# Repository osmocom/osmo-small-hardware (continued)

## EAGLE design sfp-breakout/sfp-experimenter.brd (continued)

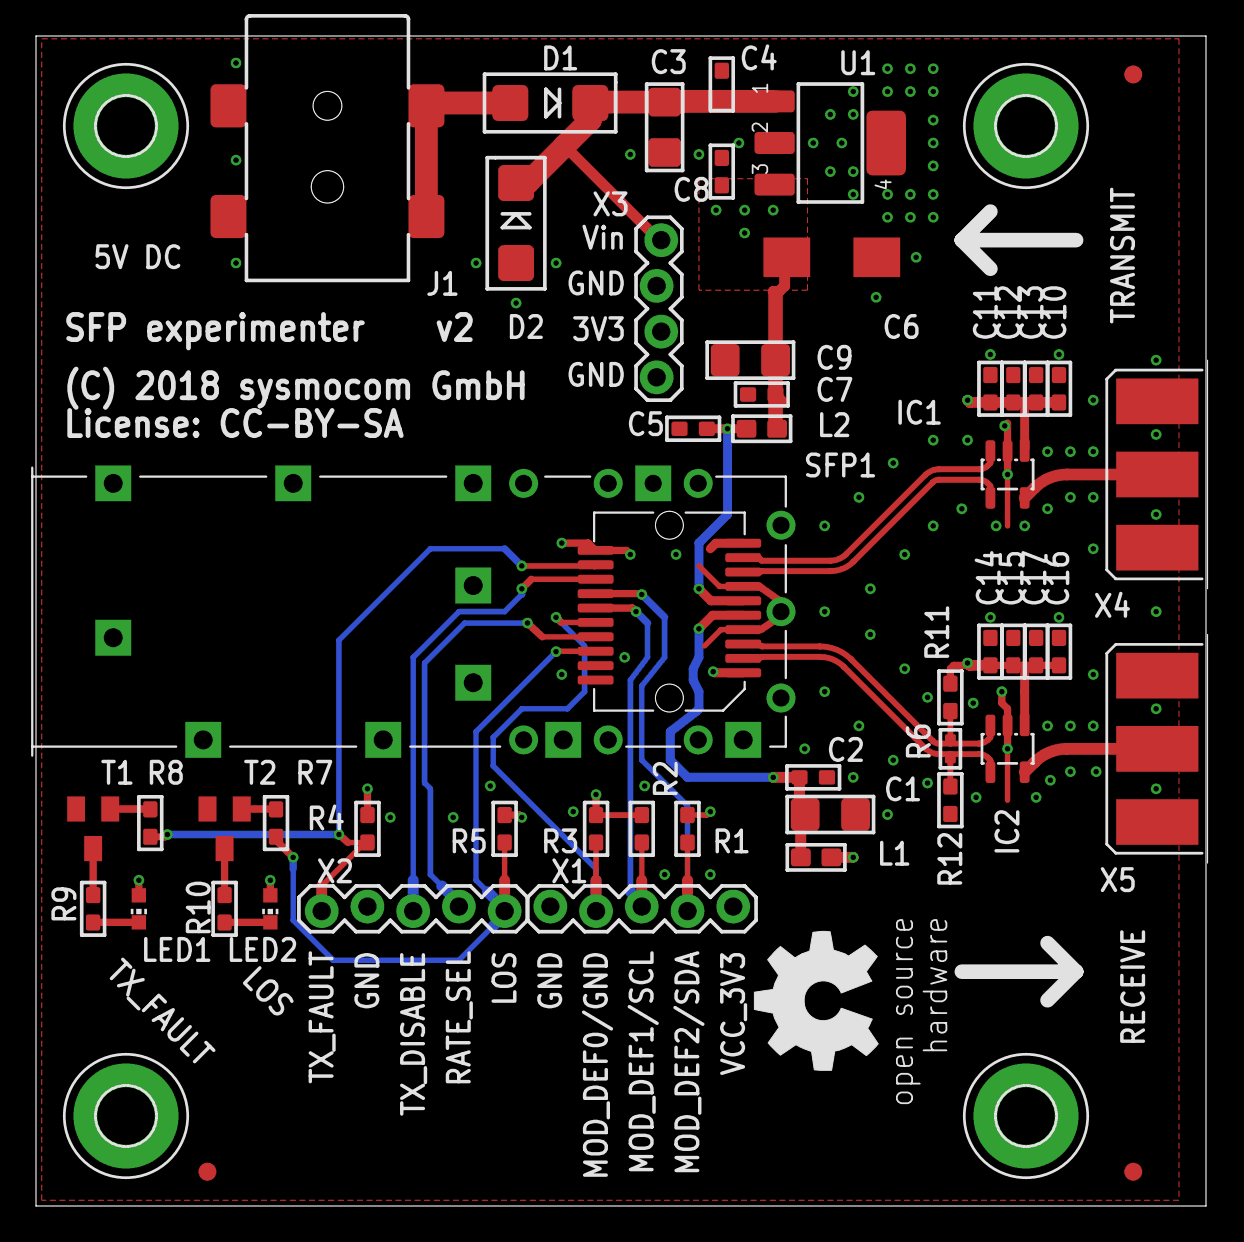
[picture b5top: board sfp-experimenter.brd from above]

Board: 4 copper layers, 65.0 x 65.0 mm, 55 parts (0 on the bottom side), 25 nets.

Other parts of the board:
U$1: OSHW_8MM

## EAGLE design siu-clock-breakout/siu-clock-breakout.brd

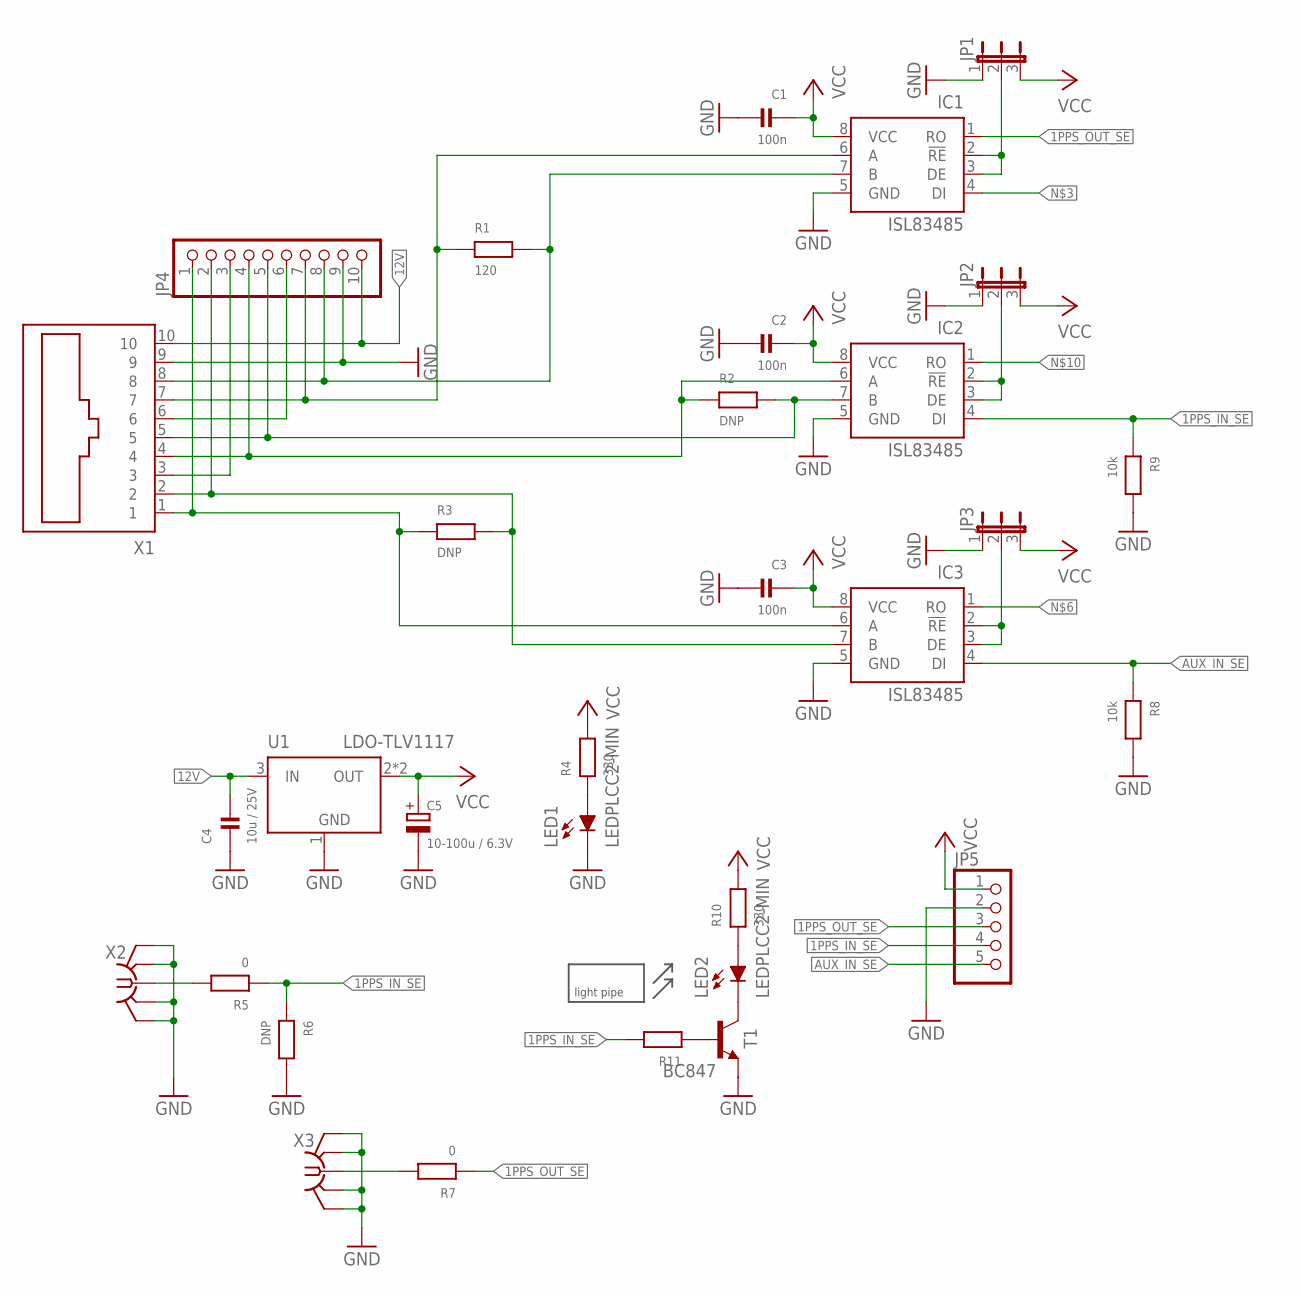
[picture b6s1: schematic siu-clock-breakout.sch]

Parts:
C1, C2, C3: 100n; _0603
C4: 10u / 25V; _0805
C5: 10-100u / 6.3V; CPOL1206
IC1, IC2, IC3: ISL83485; SOIC8
JP1, JP2, JP3: JP2E; JP2
JP4: PINHD-1X10; 1X10
JP5: PINHD-1X5; 1X05
LED1, LED2: LEDPLCC2-MIN; PLCC2-MIN
M1: MENTOR_12701001; 1270.1001
R1: 120; _0805
R2, R3: DNP; _0805
R4, R10: 330; _0603
R5, R7: 0; _0603
R6: DNP; _0603
R8, R9: 10k; _0603
R11: RESISTOR_0603; _0603
T1: BC847; SOT23-BEC; MANUFACTURERPARTNUMBER BC847C,215
U1: LDO-TLV1117; SOT223
X1: RJ45-10P10C-SS-641010-NF; SS-641010-NF
X2, X3: SMA-F-S-TH

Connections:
1PPS_IN_A: IC2.6 (A), JP4.4, R2.1, X1.4
1PPS_IN_B: IC2.7 (B), JP4.5, R2.2, X1.5
1PPS_IN_SE: IC2.4 (DI), JP5.4, R5.1, R6.1, R9.1, R11.2
1PPS_OUT_A: IC1.6 (A), JP4.7, R1.1, X1.7
1PPS_OUT_B: IC1.7 (B), JP4.8, R1.2, X1.8
1PPS_OUT_SE: IC1.1 (RO), JP5.3, R7.1
12V: C4.2, JP4.10, U1.3 (IN), X1.10
AUX_IN_A: IC3.6 (A), JP4.1, R3.1, X1.1
AUX_IN_B: IC3.7 (B), JP4.2, R3.2, X1.2
AUX_IN_SE: IC3.4 (DI), JP5.5, R8.1
GND: C1.2, C2.2, C3.2, C4.1, C5.-, IC1.5 (GND), IC2.5 (GND), IC3.5 (GND), JP1.1, JP2.1, JP3.1, JP4.9, JP5.2, LED1.K (C), R6.2, R8.2, R9.2, T1.E, U1.1 (GND), X1.9, X2.G1 (GND), X2.G2 (GND), X2.G3 (GND), X2.G4 (GND), X3.G1 (GND), X3.G2 (GND), X3.G3 (GND), X3.G4 (GND)
unnamed: LED2.A, R10.1
unnamed: LED2.K (C), T1.C
unnamed: R11.1, T1.B
unnamed: IC2.2 (!RE), IC2.3 (DE), JP2.2
unnamed: IC3.2 (!RE), IC3.3 (DE), JP3.2
unnamed: IC1.2 (!RE), IC1.3 (DE), JP1.2
unnamed: JP4.3, X1.3
unnamed: JP4.6, X1.6
unnamed: LED1.A, R4.1
unnamed: R7.2, X3.C (1)
unnamed: R5.2, X2.C (1)
VCC: C1.1, C2.1, C3.1, C5.+, IC1.8 (VCC), IC2.8 (VCC), IC3.8 (VCC), JP1.3, JP2.3, JP3.3, JP5.1, R4.2, R10.2, U1.2 (OUT), U1.4 (OUT)

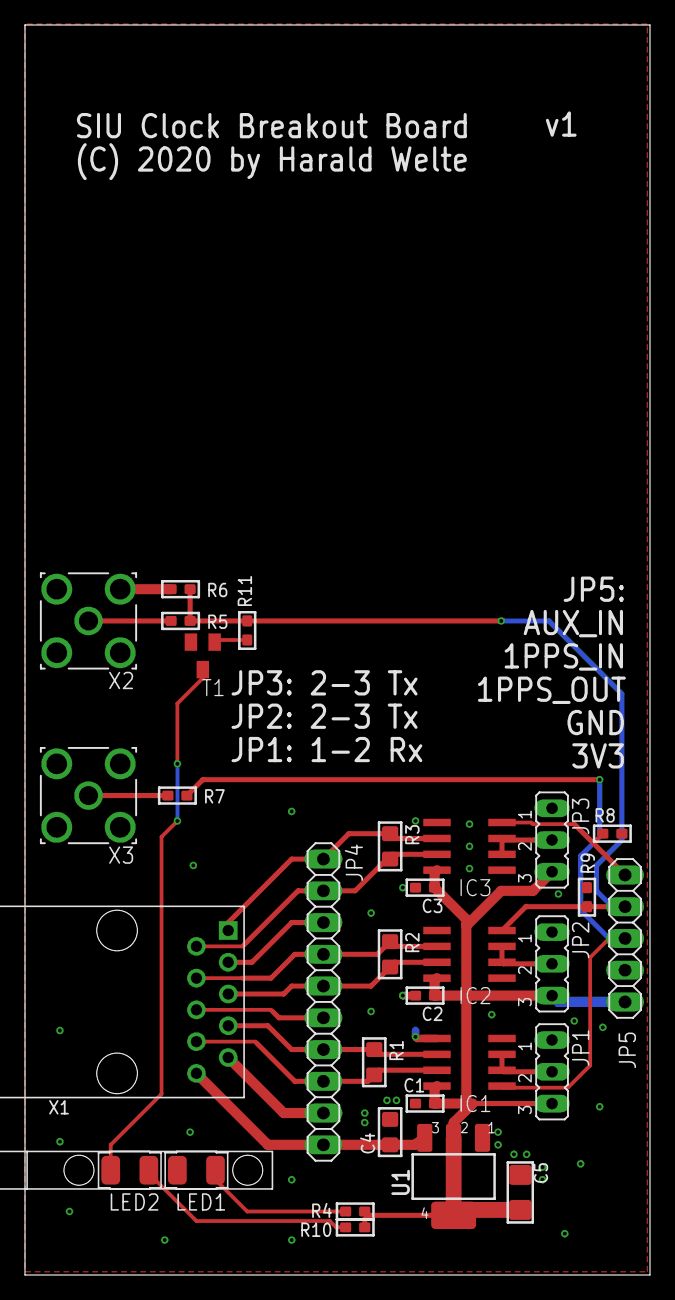
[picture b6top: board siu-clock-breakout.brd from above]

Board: 2 copper layers, 50.0 x 100.0 mm, 32 parts (0 on the bottom side), 23 nets.

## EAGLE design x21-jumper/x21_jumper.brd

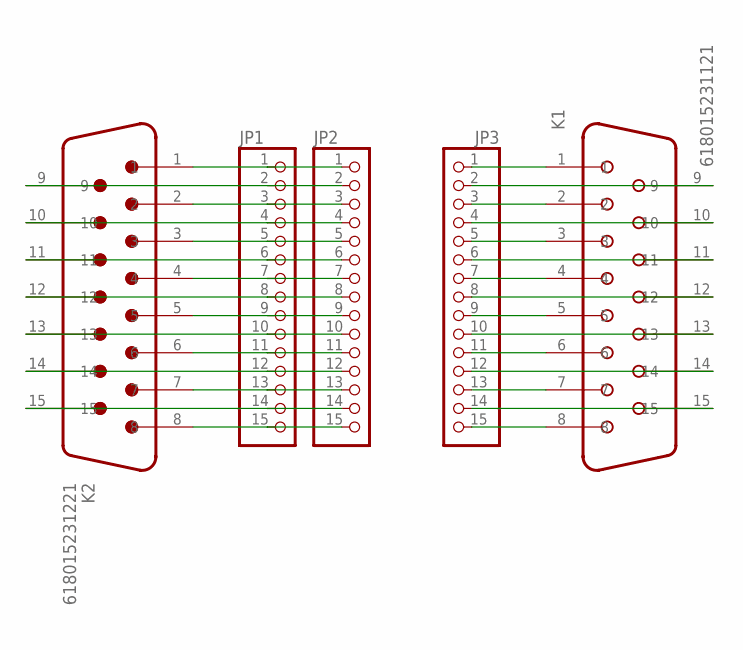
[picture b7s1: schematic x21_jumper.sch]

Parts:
JP1, JP2, JP3: PINHD-1X15; 1X15
K1: 618015231121
K2: 618015231221

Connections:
B_A_1: JP3.13, K1.7
B_A_2: JP1.13, JP2.13, K2.7
B_B_1: JP3.12, K1.14
B_B_2: JP1.12, JP2.12, K2.14
C_A_1: JP3.5, K1.3
C_A_2: JP1.5, JP2.5, K2.3
C_B_1: JP3.4, K1.10
C_B_2: JP1.4, JP2.4, K2.10
GND_1: JP3.15, K1.8
GND_2: JP1.15, JP2.15, K2.8
I_A_1: JP3.9, K1.5
I_A_2: JP1.9, JP2.9, K2.5
I_B_1: JP3.8, K1.12
I_B_2: JP1.8, JP2.8, K2.12
unnamed: JP1.14, JP2.14, K2.15
unnamed: JP3.14, K1.15
R_A_1: JP3.7, K1.4
R_A_2: JP1.7, JP2.7, K2.4
R_B_1: JP3.6, K1.11
R_B_2: JP1.6, JP2.6, K2.11
SHLD_1: JP3.1, K1.1
SHLD_2: JP1.1, JP2.1, K2.1
S_A_1: JP3.11, K1.6
S_A_2: JP1.11, JP2.11, K2.6
S_B_1: JP3.10, K1.13
S_B_2: JP1.10, JP2.10, K2.13
T_A_1: JP3.3, K1.2
T_A_2: JP1.3, JP2.3, K2.2
T_B_1: JP3.2, K1.9
T_B_2: JP1.2, JP2.2, K2.9

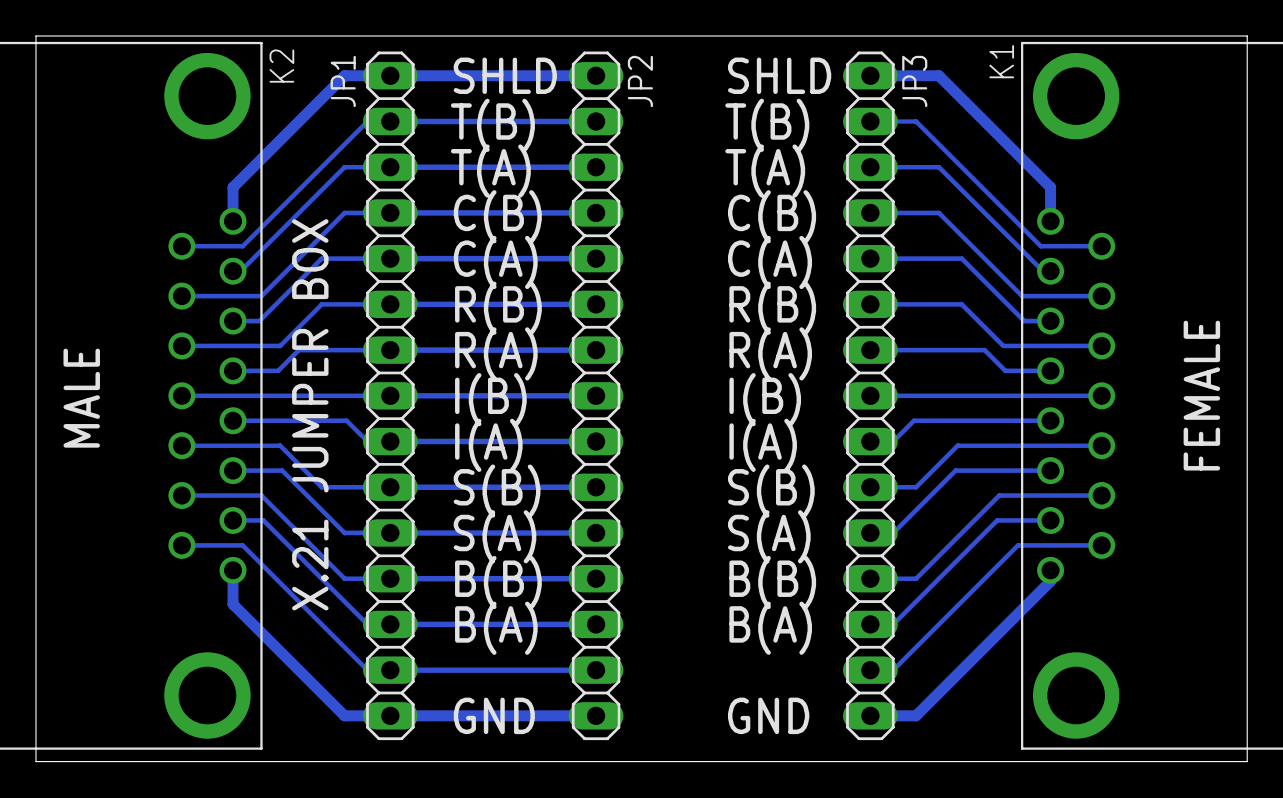
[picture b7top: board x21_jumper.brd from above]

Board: 2 copper layers, 67.3 x 40.3 mm, 5 parts (0 on the bottom side), 30 nets.

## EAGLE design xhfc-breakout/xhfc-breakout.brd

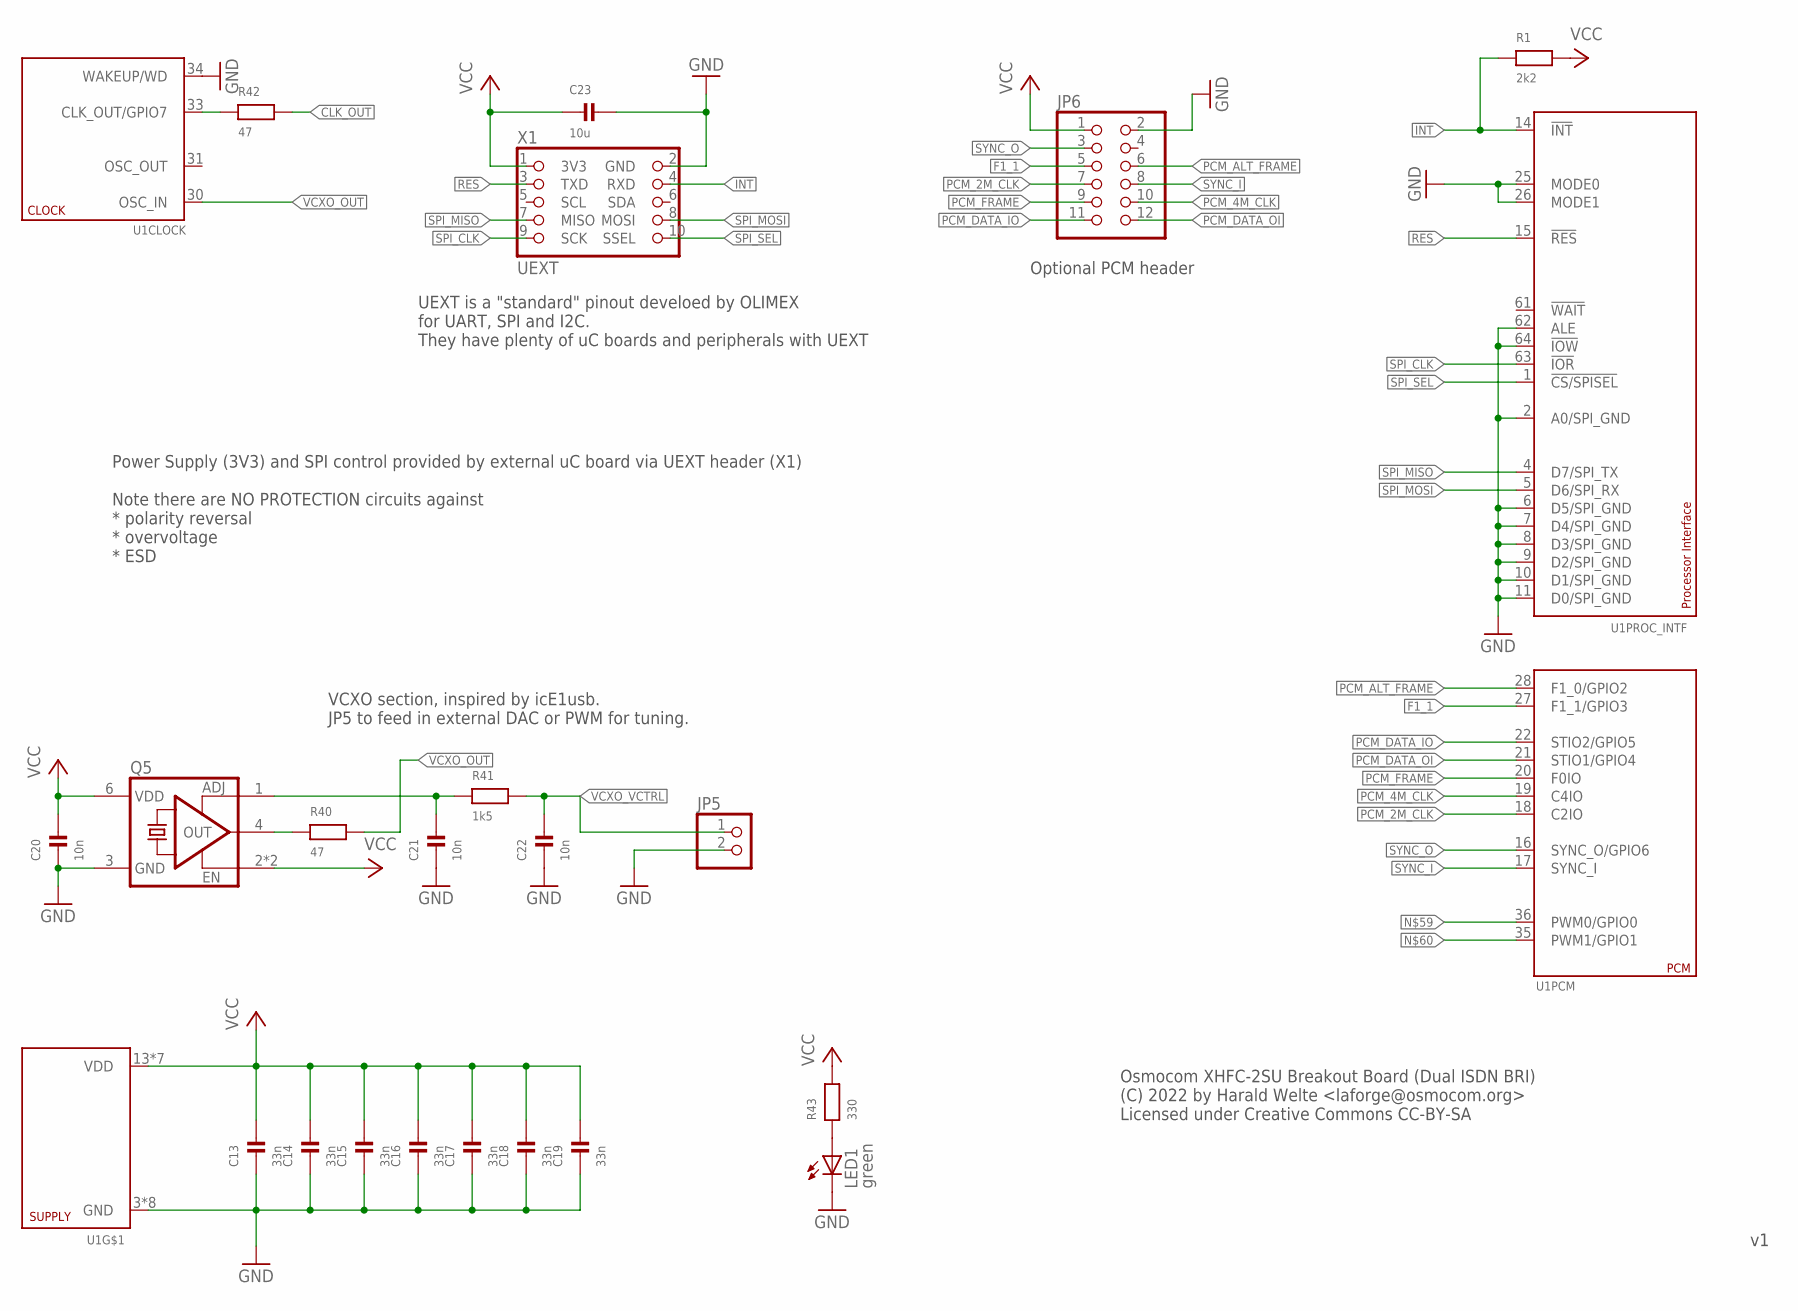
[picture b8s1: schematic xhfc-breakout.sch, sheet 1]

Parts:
C13, C14, C15, C16, C17, C18, C19: 33n; _0603; MANUFACTURERPARTNUMBER UNKNOWN MANUFACTURER PART NUMBER
C20, C21, C22: 10n; _0603; MANUFACTURERPARTNUMBER UNKNOWN MANUFACTURER PART NUMBER
C23: 10u; 1206; MANUFACTURERPARTNUMBER UNKNOWN MANUFACTURER PART NUMBER
JP5: PINHD-1X2; 1X02; MANUFACTURERPARTNUMBER UNKNOWN MANUFACTURER PART NUMBER
JP6: PINHD-2X6; 2X06; MANUFACTURERPARTNUMBER UNKNOWN MANUFACTURER PART NUMBER
LED1: green; CHIP-LED0603; MANUFACTURERPARTNUMBER UNKNOWN MANUFACTURER PART NUMBER
Q5: VCXO-EN-VKB; VKB; MANUFACTURERPARTNUMBER VKB51B2-024.576M
R1: 2k2; _0603; MANUFACTURERPARTNUMBER UNKNOWN MANUFACTURER PART NUMBER
R40, R42: 47; _0603; MANUFACTURERPARTNUMBER UNKNOWN MANUFACTURER PART NUMBER
R41: 1k5; _0603; MANUFACTURERPARTNUMBER UNKNOWN MANUFACTURER PART NUMBER
R43: 330; _0603; MANUFACTURERPARTNUMBER UNKNOWN MANUFACTURER PART NUMBER
U1: XHFC-2SU; LQFP64; MANUFACTURERPARTNUMBER XHFC-2SU
X1: UEXT; 2X05; MANUFACTURERPARTNUMBER UNKNOWN MANUFACTURER PART NUMBER

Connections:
!INT: R1.1, U1.14 (!INT), X1.4 (RXD)
!RES: U1.15 (!RES), X1.3 (TXD)
!SPI_SEL: U1.1 (!CS/SPISEL), X1.10 (SSEL)
CLK_OUT: R42.2
F1_1: JP6.5, U1.27 (F1_1/GPIO3)
GND: C13.1, C14.1, C15.1, C16.1, C17.1, C18.1, C19.1, C20.1, C21.1, C22.1, C23.2, JP5.2, JP6.2, LED1.C, Q5.3 (GND), U1.2 (A0/SPI_GND), U1.3 (GND), U1.6 (D5/SPI_GND), U1.7 (D4/SPI_GND), U1.8 (D3/SPI_GND), U1.9 (D2/SPI_GND), U1.10 (D1/SPI_GND), U1.11 (D0/SPI_GND), U1.12 (GND), U1.23 (GND), U1.25 (MODE0), U1.26 (MODE1), U1.32 (GND), U1.34 (WAKEUP/WD), U1.38 (GND), U1.45 (GND), U1.52 (GND), U1.59 (GND), U1.62 (ALE), U1.64 (!IOW), X1.2 (GND); also elsewhere on the board
unnamed: LED1.A, R43.1
unnamed: C21.2, Q5.1 (ADJ), R41.1
unnamed: R42.1, U1.33 (CLK_OUT/GPIO7)
unnamed: Q5.4 (OUT), R40.1
PCM_2M_CLK: JP6.7, U1.18 (C2IO)
PCM_4M_CLK: JP6.10, U1.19 (C4IO)
PCM_ALT_FRAME: JP6.6, U1.28 (F1_0/GPIO2)
PCM_DATA_IO: JP6.11, U1.22 (STIO2/GPIO5)
PCM_DATA_OI: JP6.12, U1.21 (STIO1/GPIO4)
PCM_FRAME: JP6.9, U1.20 (F0IO)
SPI_CLK: U1.63 (!IOR), X1.9 (SCK)
SPI_MISO: U1.4 (D7/SPI_TX), X1.7 (MISO)
SPI_MOSI: U1.5 (D6/SPI_RX), X1.8 (MOSI)
SYNC_I: JP6.8, U1.17 (SYNC_I)
SYNC_O: JP6.3, U1.16 (SYNC_O/GPIO6)
VCC: C13.2, C14.2, C15.2, C16.2, C17.2, C18.2, C19.2, C20.2, C23.1, JP6.1, Q5.2 (EN), Q5.5 (EN), Q5.6 (VDD), R1.2, R43.2, U1.13 (VDD), U1.24 (VDD), U1.29 (VDD), U1.37 (VDD), U1.44 (VDD), U1.53 (VDD), U1.60 (VDD), X1.1 (3V3); also elsewhere on the board
VCXO_OUT: R40.2, U1.30 (OSC_IN)
VCXO_VCTRL: C22.2, JP5.1, R41.2

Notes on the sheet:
UEXT is a "standard" pinout develoed by OLIMEX for UART, SPI and I2C. They have plenty of uC boards and peripherals with UEXT
Optional PCM header
VCXO section, inspired by icE1usb. JP5 to feed in external DAC or PWM for tuning.
Osmocom XHFC-2SU Breakout Board (Dual ISDN BRI) (C) 2022 by Harald Welte <laforge@osmocom.org> Licensed under Creative Commons CC-BY-SA
Power Supply (3V3) and SPI control provided by external uC board via UEXT header (X1) Note there are NO PROTECTION circuits against * polarity reversal * overvoltage * ESD

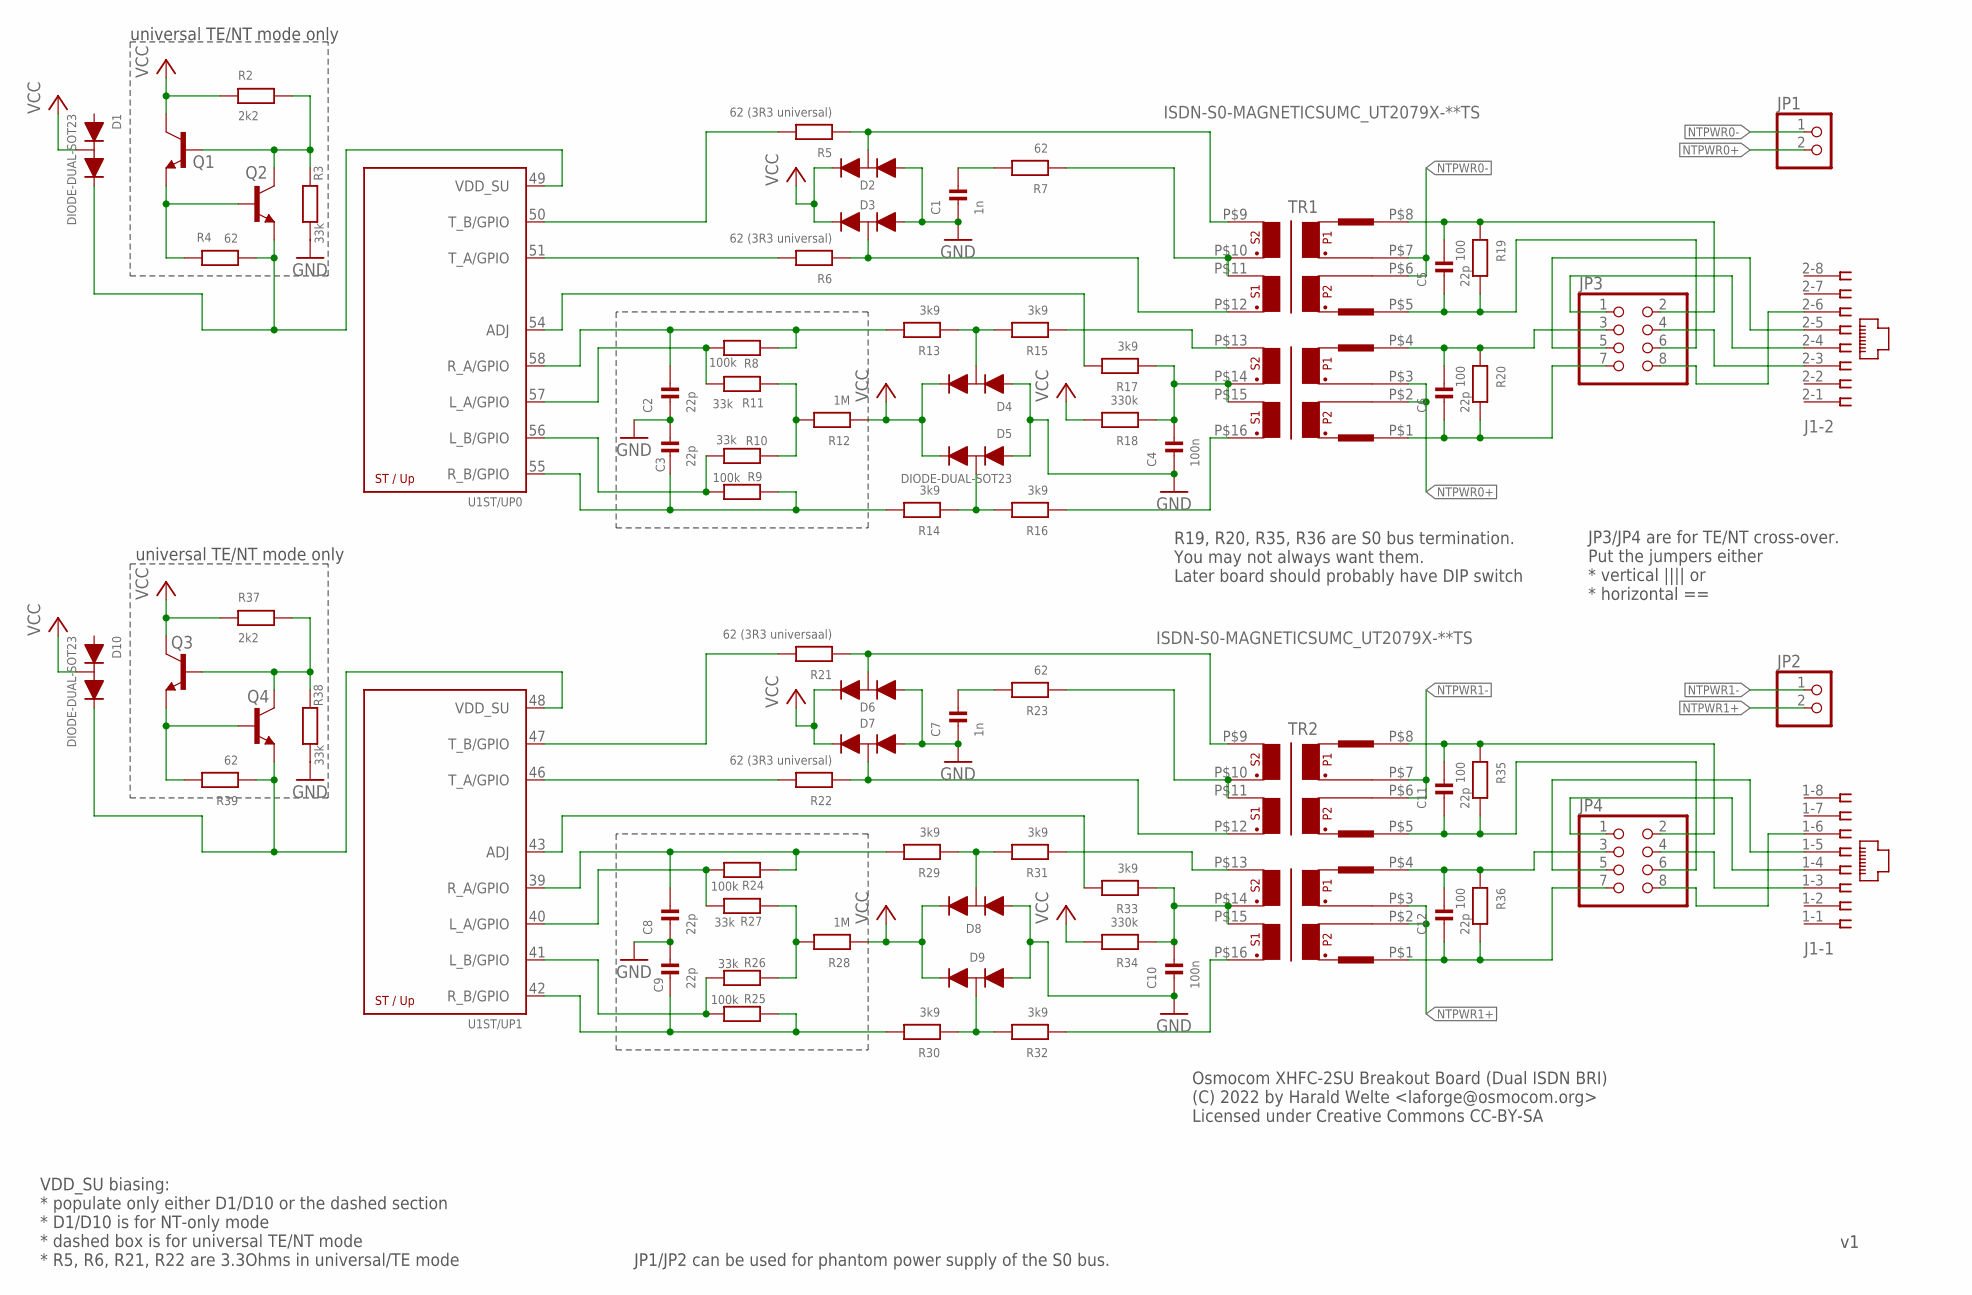
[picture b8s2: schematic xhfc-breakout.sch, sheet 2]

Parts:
C1, C7: 1n; _0603; MANUFACTURERPARTNUMBER UNKNOWN MANUFACTURER PART NUMBER
C2, C3, C5, C6, C8, C9, C11, C12: 22p; _0603; MANUFACTURERPARTNUMBER UNKNOWN MANUFACTURER PART NUMBER
C4, C10: 100n; _0603; MANUFACTURERPARTNUMBER UNKNOWN MANUFACTURER PART NUMBER
D1, D2, D3, D4, D5, D6, D7, D8, D9, D10: DIODE-DUAL-SOT23; SOT23-3; MANUFACTURERPARTNUMBER BAV99W,115
J1: 557560-1; MANUFACTURERPARTNUMBER 5557560-1
JP1, JP2: PINHD-1X2; 1X02; MANUFACTURERPARTNUMBER UNKNOWN MANUFACTURER PART NUMBER
JP3, JP4: PINHD-2X4; 2X04; MANUFACTURERPARTNUMBER UNKNOWN MANUFACTURER PART NUMBER
Q1, Q2, Q3, Q4: BC848CSMD; SOT23; MANUFACTURERPARTNUMBER BC848CWT1G
R2, R37: 2k2; _0603; MANUFACTURERPARTNUMBER UNKNOWN MANUFACTURER PART NUMBER
R3, R10, R11, R26, R27, R38: 33k; _0603; MANUFACTURERPARTNUMBER UNKNOWN MANUFACTURER PART NUMBER
R4, R7, R23, R39: 62; _0603; MANUFACTURERPARTNUMBER UNKNOWN MANUFACTURER PART NUMBER
R5, R6, R22: 62 (3R3 universal); _0603; MANUFACTURERPARTNUMBER UNKNOWN MANUFACTURER PART NUMBER
R8, R9, R24, R25: 100k; _0603; MANUFACTURERPARTNUMBER UNKNOWN MANUFACTURER PART NUMBER
R12, R28: 1M; _0603; MANUFACTURERPARTNUMBER UNKNOWN MANUFACTURER PART NUMBER
R13, R14, R15, R16, R17, R29, R30, R31, R32, R33: 3k9; _0603; MANUFACTURERPARTNUMBER UNKNOWN MANUFACTURER PART NUMBER
R18, R34: 330k; _0603; MANUFACTURERPARTNUMBER UNKNOWN MANUFACTURER PART NUMBER
R19, R20, R35, R36: 100; _0603; MANUFACTURERPARTNUMBER UNKNOWN MANUFACTURER PART NUMBER
R21: 62 (3R3 universaal); _0603; MANUFACTURERPARTNUMBER UNKNOWN MANUFACTURER PART NUMBER
TR1, TR2: ISDN-S0-MAGNETICSUMC_UT2079X-**TS; UMEC_UT207; MANUFACTURERPARTNUMBER UT20795-5MTS
U1: XHFC-2SU; LQFP64; MANUFACTURERPARTNUMBER XHFC-2SU

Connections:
GND: C1.1, C2.1, C3.2, C4.1, C7.1, C8.1, C9.2, C10.1, D2.1 (A), D3.1 (A), D4.1 (A), D5.1 (A), D6.1 (A), D7.1 (A), D8.1 (A), D9.1 (A), R3.1, R38.1; also elsewhere on the board
unnamed: Q1.1 (B), Q2.3 (C), R2.2, R3.2
unnamed: Q1.2 (E), Q2.1 (B), R4.2
unnamed: D2.3 (M), R5.1, TR1.P$9 (9)
unnamed: D3.3 (M), R6.1, TR1.P$12 (12)
unnamed: J1.2-4 (4), JP3.1
unnamed: C1.2, R7.2
unnamed: R7.1, TR1.P$10 (10), TR1.P$11 (11)
unnamed: R10.1, R11.1, R12.2
unnamed: D6.3 (M), R21.1, TR2.P$9 (9)
unnamed: C5.2, JP3.2, R19.1, TR1.P$8 (8)
unnamed: D4.3 (M), R13.1, R15.2
unnamed: D5.3 (M), R14.1, R16.2
unnamed: C5.1, JP3.6, R19.2, TR1.P$5 (5)
unnamed: R15.1, TR1.P$13 (13)
unnamed: R16.1, TR1.P$16 (16)
unnamed: C4.2, R17.1, R18.1, TR1.P$14 (14), TR1.P$15 (15)
unnamed: J1.2-5 (5), JP3.5
unnamed: C6.1, JP3.7, R20.2, TR1.P$1 (1)
unnamed: D7.3 (M), R22.1, TR2.P$12 (12)
unnamed: C7.2, R23.2
unnamed: R23.1, TR2.P$10 (10), TR2.P$11 (11)
unnamed: R26.1, R27.1, R28.2
unnamed: D8.3 (M), R29.1, R31.2
unnamed: D9.3 (M), R30.1, R32.2
unnamed: R31.1, TR2.P$13 (13)
unnamed: R32.1, TR2.P$16 (16)
unnamed: C10.2, R33.1, R34.1, TR2.P$14 (14), TR2.P$15 (15)
unnamed: C11.2, JP4.2, R35.1, TR2.P$8 (8)
unnamed: C11.1, JP4.6, R35.2, TR2.P$5 (5)
unnamed: C12.2, JP4.3, R36.1, TR2.P$4 (4)
unnamed: C12.1, JP4.7, R36.2, TR2.P$1 (1)
unnamed: Q3.1 (B), Q4.3 (C), R37.2, R38.2
unnamed: Q3.2 (E), Q4.1 (B), R39.2
unnamed: C6.2, JP3.3, R20.1, TR1.P$4 (4)
unnamed: J1.2-3 (3), JP3.4
unnamed: J1.2-6 (6), JP3.8
unnamed: J1.1-4 (4), JP4.1
unnamed: J1.1-5 (5), JP4.5
unnamed: J1.1-3 (3), JP4.4
unnamed: J1.1-6 (6), JP4.8
NTPWR0+: JP1.2, TR1.P$2 (2), TR1.P$3 (3)
NTPWR0-: JP1.1, TR1.P$6 (6), TR1.P$7 (7)
NTPWR1+: JP2.2, TR2.P$2 (2), TR2.P$3 (3)
NTPWR1-: JP2.1, TR2.P$6 (6), TR2.P$7 (7)
P0_ADJ: R17.2, U1.54 (ADJ)
P0_L_A: R8.2, R11.2, U1.57 (L_A/GPIO)
P0_L_B: R9.2, R10.2, U1.56 (L_B/GPIO)
P0_R_A: C2.2, R8.1, R13.2, U1.58 (R_A/GPIO)
P0_R_B: C3.1, R9.1, R14.2, U1.55 (R_B/GPIO)
P0_T_A: R6.2, U1.51 (T_A/GPIO)
P0_T_B: R5.2, U1.50 (T_B/GPIO)
P0_VDD_SU: D1.2 (C), Q2.2 (E), R4.1, U1.49 (VDD_SU)
P1_ADJ: R33.2, U1.43 (ADJ)
P1_L_A: R24.2, R27.2, U1.40 (L_A/GPIO)
P1_L_B: R25.2, R26.2, U1.41 (L_B/GPIO)
P1_R_A: C8.2, R24.1, R29.2, U1.39 (R_A/GPIO)
P1_R_B: C9.1, R25.1, R30.2, U1.42 (R_B/GPIO)
P1_T_A: R22.2, U1.46 (T_A/GPIO)
P1_T_B: R21.2, U1.47 (T_B/GPIO)
P1_VDD_SU: D10.2 (C), Q4.2 (E), R39.1, U1.48 (VDD_SU)
VCC: D1.3 (M), D2.2 (C), D3.2 (C), D4.2 (C), D5.2 (C), D6.2 (C), D7.2 (C), D8.2 (C), D9.2 (C), D10.3 (M), Q1.3 (C), Q3.3 (C), R2.1, R12.1, R18.2, R28.1, R34.2, R37.1; also elsewhere on the board

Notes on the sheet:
universal TE/NT mode only
VDD_SU biasing: * populate only either D1/D10 or the dashed section * D1/D10 is for NT-only mode * dashed box is for universal TE/NT mode * R5, R6, R21, R22 are 3.3Ohms in universal/TE mode
R19, R20, R35, R36 are S0 bus termination. You may not always want them. Later board should probably have DIP switch
JP3/JP4 are for TE/NT cross-over. Put the jumpers either * vertical |||| or * horizontal ==
JP1/JP2 can be used for phantom power supply of the S0 bus.
Osmocom XHFC-2SU Breakout Board (Dual ISDN BRI) (C) 2022 by Harald Welte <laforge@osmocom.org> Licensed under Creative Commons CC-BY-SA

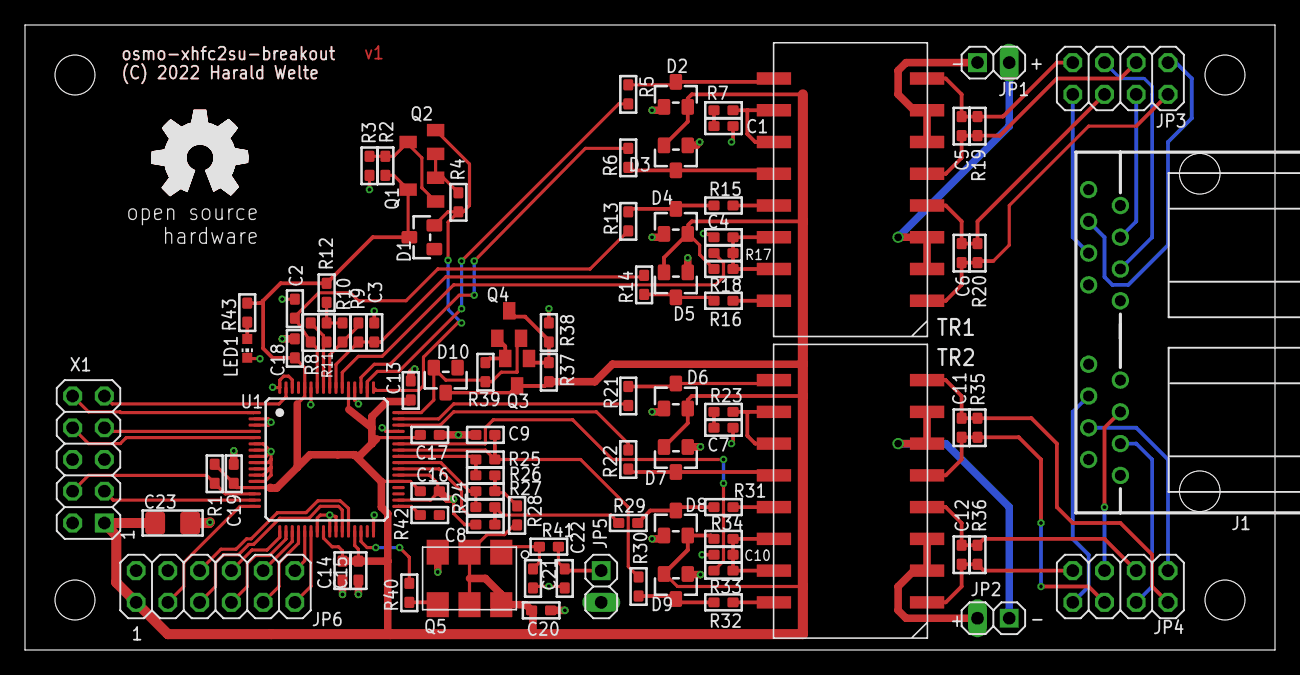
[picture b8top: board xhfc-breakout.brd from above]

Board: 2 copper layers, 100.0 x 50.0 mm, 95 parts (0 on the bottom side), 83 nets.

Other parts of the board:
U$1: OSHW_8MM_COPPER
U$2: OSHW_8MM
